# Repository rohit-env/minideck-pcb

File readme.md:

# Rohit's minideck PCB

so I went off and designed a whole cyberdeck pcb, it’s kinda sick, it's a full-on deck with ports, buttons, blinky stuff, and that clean hacker aesthetic. built it because laptops are boring and carrying around raw PCBs just hits different.the board’s got space for a pi, a couple usb ports, an oled, and some clicky switches. stuff’s laid out in a way that makes sense, but also makes you look like you’re about to jack into the matrix at a coffee shop. the idea is simple cram as much functional coolness as possible onto one board and still make it portable enough to flex at meetups. this whole thing started with a sketch on a sticky note and now it’s a real life project(obviously i need money to make it real). i even left space for expansion headers because future proofing or whatever. no idea how many late nights went into routing this lol

---

# features 

Uses Raspberry-pi CM4 form-factor for main SBC.

5inch or 4.3inch LCD display with support for another External Display out port.

Uses ESP32-S2 for all the secondary functions including keyboard and mouse control.

61 key customizable keyboard, 6 shoulder button for navigation.

3D hall-effect joystick is used for proper Mouse control.

10000mAh(21700) 2S battery can be used for main power source.

USB-PD 2Amps fast charging using USB-C port.

One USB-A and display out for external display.

USB-C formfactor Nurolink/docking port with UART, I2C.

---

| Image | Description |
|-------|-------------|
|  | top |

| Image | Description |
|-------|-------------|
|  | side |

| Image | Description |
|-------|-------------|
|  | top side |

| Image | Description |
|-------|-------------|
|  | main pcb render |

| Image | Description |
|-------|-------------|
|  | display pcb render |

| Image | Description |
|-------|-------------|
|  | main pcb |

| Image | Description |
|-------|-------------|
|   | display pcb |

----

# BOM

| **Component**            | **Description**                                                 | **Qty**     | **Estimated Price (USD)** | **Link** |
|--------------------------|-----------------------------------------------------------------|-------------|----------------------------|----------|
| **PCB**                  | Custom PCB                                           | 1           | $92 (without pcba after $20 coupon) | JLCPCB  |
| **4.3 inch display**     | Display for the deck                                            | 1           | $36.16                     | [Robocraze](https://robocraze.com/products/waveshare-4-3inch-dsi-lcd-capacitive-touch-display-800-480-for-raspberry-pi) |
| **21700 batteries**      | Batteries                                                       | 1 (pair)    | $10.41                     | [Drkstore](https://www.drkstore.in/molicel-inr-21700-p45b-3-6v-4500mah-10c-li-ion-battery/) |
| **5V Voltage Regulator** | Power regulator for the display                                 | 2           | $11.76                     | [Robocraze](https://robocraze.com/products/dfrobot-multi-output-dc-dc-buck-converter-module-3-3v-5v-9v-12v?variant=47357264396512) |
| **ESP32 Microcontroller**| Controls everything in the device (keyboard, mouse, etc.)       | 1           | $0                         | Already available |
| **Raspberry Pi Compute Module** | Heart of the device                                      | 1           | $80                        | [Robu](https://robu.in/product/raspberry-pi-compute-module-5-2gb-32gb/?gad_source=1&gad_campaignid=19974686076&gbraid=0AAAAADvLFWcZy6YV9cw0LotGvW8Dvi9Ij&gclid=CjwKCAjwkbzEBhAVEiwA4V-yqq5n8SdlHlythZ7EGNnsObi1siXfHtQSt-FhHNs-aKGvbE-3w4f5ixoC-zMQAvD_BwE) |

BOM: $229

# gallery

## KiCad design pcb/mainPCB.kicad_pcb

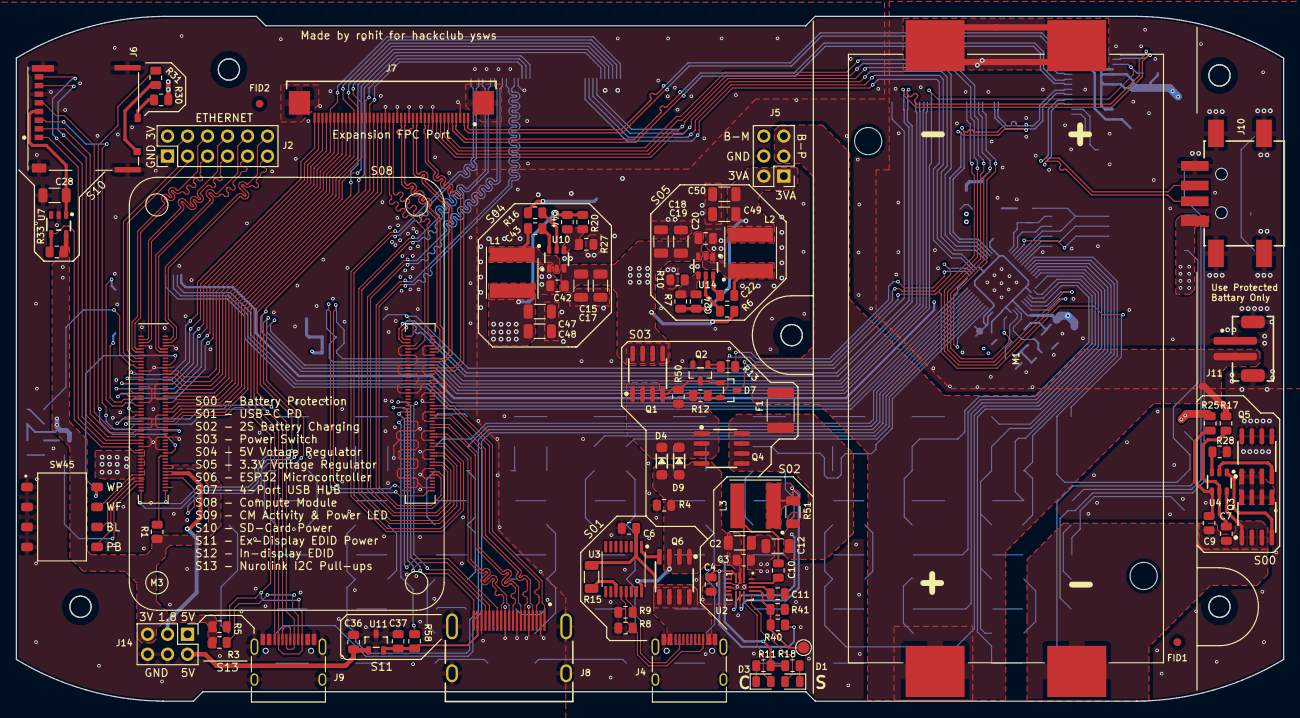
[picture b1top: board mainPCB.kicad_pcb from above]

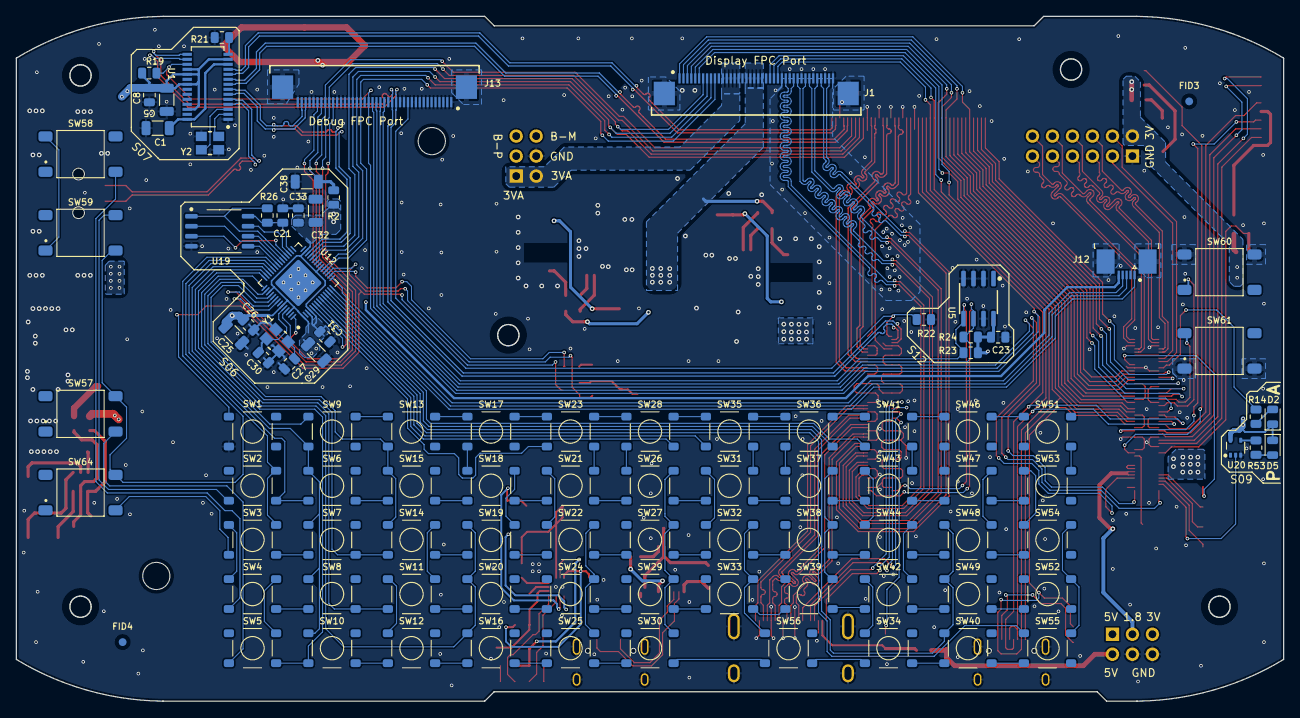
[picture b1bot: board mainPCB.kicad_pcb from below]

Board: 4 copper layers, 161.0 x 87.0 mm, 194 parts (97 on the bottom side), 260 nets.

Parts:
C1, C5, C15, C17, C18, C19, C25, C28, C29, C32, C38: 10uF; Capacitor-1206
C2, C12, C47, C48, C49, C50: 22uF; Capacitor-1206
C3, C4, C6, C11: 1uF; Capacitor-0805
C7, C8, C9, C10, C20, C21, C22, C23, C26, C31, C33, C36, C37, C42, C43: 0.1uF; Capacitor-0805
C24, C44: 100pF; Capacitor-0805
C27, C30: 16pF; Capacitor-0805
D1, D2, D3, D5: LED; LED-0805
D4, D9: MBR0540T3G; Diode-SOD-123
D7: BAT54C-(SOT23); SOT-23-3
F1: 0ZCG0260BF2B; Fuse-1812
FID1, FID2, FID3, FID4: Fiducial; Fiducial_1mm_Mask2mm
H1, H2, H3, H4, H5: MountingHole_Pad; MountingHole-M2.5-D2.7mm
J1, J7, J13: CF20401D0R0-NH; FPC-40-0.5mm-horizontal
J2: Conn_02x06-(RS2-12-G); PinHeader_2x06_P2.54mm_Vertical
J4, J9: 12402012E212A; USB_C-Female-(16-Pin)
J5, J14: Conn_02x03-(RS2-06-G); PinHeader_2x03_P2.54mm_Vertical
J6: Micro_SD_Card_Det; SD-Micro-Push-Push(MOLEX_503398-1892)
J8: HDMI_A-(2086581051); HDMI(EDAC 690-019-298-412)
J10: 629104190121; USB_A-horizontal-SMD-3
J11: B2B-PH-SM4-TB; JST-PH2-Vertical
J12: SFV5R-2STBE1HLF; FPC-5-0.5mm-horizontal
L1, L2: 10uH-(74404064100); Inductor-6.0x6.0xH4.5
L3: 6.8uH-(74404064068); Inductor-6.0x6.0xH4.5
M1: keystone-PN1048; Battery_holder-18650x2(keystone-PN1048)
M3: DF40C-100DS-0.4V(51); Module-ComputeModule4-CM4
Q1, Q4: DMP3037LSS-13; SOP-8
Q2: BCW66HVL-(2N2222); SOT-23-3
Q3, Q5: MOSFET-N; SOP-8
Q6: AOSP36326C; SOP-8
R1, R22, R28: 2.2k; Resistor-0805
R2, R3, R4, R5, R10, R12, R27, R40, R41, R50, R58: 10k; Resistor-0805
R6, R16, R19, R23, R24, R26, R33: 100k; Resistor-0805
R7: 33.2K; Resistor-0805
R8, R9: 5.1k; Resistor-0805
R11, R14, R18, R53: 1k; Resistor-0805
R13, R30, R31: 220R; Resistor-0805
R15: 5.1k; Resistor-1206
R17, R25: 330R; Resistor-0805
R20: 56.2k; Resistor-0805
R21: 2.7k; Resistor-0805
R51: 50mR; Resistor-1206
SW1, SW2, SW3, SW4, SW5, SW6, SW7, SW8, SW9, SW10, SW11, SW12, SW13, SW14, SW15, SW16, SW17, SW18, SW19, SW20, SW21, SW22, SW23, SW24, SW25, SW26, SW27, SW28, SW29, SW30, SW31, SW32, SW33, SW34, SW35, SW36, SW37, SW38, SW39, SW40, SW41, SW42, SW43, SW44, SW46, SW47, SW48, SW49, SW51, SW52, SW53, SW54, SW55, SW56: PTS526 SK15 SMTR2 LFS-(C&K); Switch-4x4x1.5-(PTS526)
SW45: Switch-6.2X4-DIP(DS04-254-2-04BK)
SW57, SW58, SW59, SW60, SW61, SW64: TS04-66-85-BK-160-SMT; Switch-6x6xXX-Extend
TP16: THERM; TestPoint-Pad_D1.5mm
U1: FE1.1S-BSOP28BCN; SSOP-28 (3.9x9.9x0.635)
U2: MP2615CGQ-Z-(QFN-16); QFN-16 (3x3-MP2615)
U3: IP2721-(TSSOP-16); TSSOP-16
U4: MM3220/S8252-(SOT-23-6); SOT-23-6
U5: AT24CM01-SSHM-B; SOP-8
U7: RT9742GGJ5; SOT-23-5
U10, U14: AP62300TWU-7-(SOT-23-6); SOT-23-6
U11: RT9742SNGV; SOT-23-3
U12: ESP32-S2FH4; QFN-56 (7x7x0.4)
U19: W25Q128JVS; SOIC-8-208mil
U20: 74LVC1G07SE-7-(SOT-353); SOT-353
Y1: 40mhz-(RH100-40.000-16-F-1010-TR); Crystal-3225-SMD
Y2: 12MHz-(RH100-12.000-12-1010-X-TR-NS2); Crystal-3225-SMD

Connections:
1: SW2.4, SW3.4, U12.38 (GPIO34)
1D+: J10.3 (D+), U1.5 (DP4)
1D-: J10.2 (D-), U1.4 (DM4)
2: SW6.3, SW7.3, SW8.3, SW9.1, SW10.3, U12.40 (GPIO36)
2D+: J13.39, U1.7 (DP3), U12.26 (GPIO20/USB_P)
2D-: J13.38, U1.6 (DM3), U12.25 (GPIO19/USB_N)
3: SW13.1, SW14.3, SW15.3, U12.47 (GPIO42)
3D+: J7.4, U1.9 (DP2)
3D-: J7.5, U1.8 (DM2)
4: SW16.3, SW19.3, SW20.3, U12.43 (GPIO39)
4D+: J7.1, U1.11 (DP1)
4D-: J7.2, U1.10 (DM1)
5: SW23.1, U12.6 (GPIO1)
6: SW28.2, U12.7 (GPIO2)
7: SW35.1, U12.8 (GPIO3)
8: SW36.2, U12.11 (GPIO6)
9: SW41.1, U12.12 (GPIO7)
10: SW40.3, SW48.3, SW49.3, U12.10 (GPIO5)
11: SW55.3, U12.9 (GPIO4)
12: SW57.4, SW59.2, SW64.4, U12.37 (GPIO33)
+3.3V: D2.A, D5.A, J2.2, J14.5, M3.84 (+3.3v_(Output)), M3.86 (+3.3v_(Output)), R1.1, R3.1, R5.1, R30.1, R33.1, U7.5 (IN), U20.5 (VCC)
+3.3VA: C5.1, C8.1, C24.2, C25.2, C26.2, C29.2, C31.2, C32.2, C33.2, C49.2, C50.2, J1.12, J1.13, J1.14, J1.15, J1.16, J5.1, J5.2, J12.5, L2.2, R2.2, R7.1, R19.2, U1.13 (VD33), U1.18 (VBUSM), U1.19 (BUSJ), U1.21 (VD33_O), U1.26 (OVCJ), U12.1 (VDDA), U12.3 (VDD3P3), U12.4 (VDD3P3), U12.20 (VDD3P3_RTC), U12.27 (VDD3P3_RTC_IO), U12.45 (VDD3P3_CPU), U12.51 (VDDA), U12.54 (VDDA)
+5V: C23.2, C36.1, C44.2, C47.2, C48.2, J10.1 (VBUS), J14.1, J14.2, L1.2, M3.77 (+5v_(Input)), M3.79 (+5v_(Input)), M3.81 (+5v_(Input)), M3.83 (+5v_(Input)), M3.85 (+5v_(Input)), M3.87 (+5v_(Input)), R20.1, R23.2, R24.2, U5.8 (VCC), U11.1 (IN)
+12V: C2.2, C3.2, D4.A, D9.A, Q4.4, Q6.1, Q6.2, Q6.3, R4.1, R11.2, R18.2, U2.2 (VIN), U3.16 (VBUS)
+BATT: F1.2, J5.3, J5.5, J11.2, M1.1, R17.1
+VDC: C12.2, F1.1, Q4.5, Q4.6, Q4.7, Q4.8, R51.1, U2.9 (BATT)
-BATT: C7.1, C9.1, M1.3, Q3.1, Q3.2, Q3.3, U4.6 (GND)
/+1.8v: J14.3, M3.88 (+1.8v_(Output)), M3.90 (+1.8v_(Output))
/ACOK: D1.C, U2.12 (*ACOK)
/Activity_LED: M3.21 (PI_nLED_Activity), R14.2
/BT_nDis: M3.91 (BT_nDisable), SW45.3B
/Charger_SW_Out: L3.1, R51.2, U2.10 (CSP)
/EEPROM_nWP: M3.20 (EEPROM_nWP), SW45.1B
/ETH_0_N: J2.9, M3.10 (Ethernet_Pair0_N)
/ETH_0_P: J2.10, M3.12 (Ethernet_Pair0_P)
/ETH_1_N: J2.11, M3.6 (Ethernet_Pair1_N)
/ETH_1_P: J2.12, M3.4 (Ethernet_Pair1_P)
/ETH_2_N: J2.5, M3.9 (Ethernet_Pair2_N)
/ETH_2_P: J2.6, M3.11 (Ethernet_Pair2_P)
/ETH_3_N: J2.7, M3.5 (Ethernet_Pair3_N)
/ETH_3_P: J2.8, M3.3 (Ethernet_Pair3_P)
/ETH_LEDG: J2.4, M3.17 (Ethernet_nLED2(3.3v))
/ETH_LEDY: J2.3, M3.15 (Ethernet_nLED3(3.3v))
/GLOBAL_EN: J13.21, M3.99 (Global_EN)
/GPIO2: J1.26, J7.26, J9.A5 (CC1), J9.B5 (CC2), M3.58 (GPIO2), R5.2
/GPIO3: J1.25, J7.27, J9.A8 (SBU1), J9.B8 (SBU2), M3.56 (GPIO3), R3.2
/GPIO4: J1.24, M3.54 (GPIO4)
/GPIO6: J7.31, M3.30 (GPIO6)
/GPIO7: J7.37, M3.37 (GPIO7)
/GPIO8: J1.1, J7.36, M3.39 (GPIO8)
/GPIO9: J1.3, J7.29, M3.40 (GPIO9)
/GPIO10: J1.4, J7.28, M3.44 (GPIO10)
/GPIO11: J1.2, J7.30, M3.38 (GPIO11)
/GPIO12: J7.38, M3.31 (GPIO12)
/GPIO13: J7.32, M3.28 (GPIO13)
/GPIO14: J7.25, J9.A7 (D-), J9.B7 (D-), M3.55 (GPIO14)
/GPIO15: J7.24, J9.A6 (D+), J9.B6 (D+), M3.51 (GPIO15)
/GPIO17: J1.5, M3.50 (GPIO17)
/GPIO18: J7.35, M3.49 (GPIO18)
/GPIO19: J7.33, M3.26 (GPIO19)
/GPIO20: J7.39, M3.27 (GPIO20)
/GPIO21: J7.40, M3.25 (GPIO21)
/GPIO24: M3.45 (GPIO24), SW60.1
/GPIO25: M3.41 (GPIO25), SW61.3
/GPIO26: J7.34, M3.24 (GPIO26)
/GPIO27: J1.6, M3.48 (GPIO27)
/GPIO_VREF: M3.78 (GPIO_VREF(1.8v/3.3v_Input)), R1.2
/HDMI0_CK_N: J1.28, M3.190 (HDMI0_CLK_N)
/HDMI0_CK_P: J1.30, M3.188 (HDMI0_CLK_P)
/HDMI0_D0_N: J1.31, M3.184 (HDMI0_TX0_N)
/HDMI0_D0_P: J1.33, M3.182 (HDMI0_TX0_P)
/HDMI0_D1_N: J1.34, M3.178 (HDMI0_TX1_N)
/HDMI0_D1_P: J1.36, M3.176 (HDMI0_TX1_P)
/HDMI0_D2_N: J1.37, M3.172 (HDMI0_TX2_N)
/HDMI0_D2_P: J1.39, M3.170 (HDMI0_TX2_P)
/HDMI0_HOTPLUG: M3.153 (HDMI0_HOTPLUG), R58.2
/HDMI0_SCL: J13.19, M3.200 (HDMI0_SCL), R24.1, U5.6 (SCL)
/HDMI0_SDA: J13.18, M3.199 (HDMI0_SDA), R23.1, U5.5 (SDA)
/HDMI1_CEC: J8.13 (CEC), M3.149 (HDMI1_CEC)
/HDMI1_CK_N: J8.12 (CK-), M3.166 (HDMI1_CLK_N)
/HDMI1_CK_P: J8.10 (CK+), M3.164 (HDMI1_CLK_P)
/HDMI1_D0_N: J8.9 (D0-), M3.160 (HDMI1_TX0_N)
/HDMI1_D0_P: J8.7 (D0+), M3.158 (HDMI1_TX0_P)
/HDMI1_D1_N: J8.6 (D1-), M3.154 (HDMI1_TX1_N)
/HDMI1_D1_P: J8.4 (D1+), M3.152 (HDMI1_TX1_P)
/HDMI1_D2_N: J8.3 (D2-), M3.148 (HDMI1_TX2_N)
/HDMI1_D2_P: J8.1 (D2+), M3.146 (HDMI1_TX2_P)
/HDMI1_HOTPLUG: J8.19 (HPD/HEAC-), M3.143 (HDMI1_HOTPLUG)
/HDMI1_SCL: J8.15 (SCL), M3.147 (HDMI1_SCL)
/HDMI1_SDA: J8.16 (SDA), M3.145 (HDMI1_SDA)
/HDMI_5v: C37.1, J8.18 (+5V), R58.1, U11.2 (OUT)
/PCIE_CLK_N: J7.17, M3.112 (PCIe_CLK_N)
/PCIE_CLK_P: J7.18, M3.110 (PCIe_CLK_P)
/PCIE_CLK_nREQ: J7.20, M3.102 (PCIe_CLK_nREQ)
/PCIE_RX_N: J7.14, M3.118 (PCIe_RX_N)
/PCIE_RX_P: J7.15, M3.116 (PCIe_RX_P)
/PCIE_TX_N: J7.11, M3.124 (PCIe_TX_N)
/PCIE_TX_P: J7.12, M3.122 (PCIe_TX_P)
/PCIE_nRST: J7.21, M3.109 (PCIe_nRST)
/PWR_LED: M3.95 (nPI_LED_PWR), U20.2
/RUN_PG: J13.20, M3.92 (RUN_PG)
/Reserved: M3.76 (Reserved), R31.1
/SD_CLK: J6.5 (CLK), M3.57 (SD_CLK)
/SD_CMD: J6.3 (CMD), M3.62 (SD_CMD)
/SD_DAT0: J6.7 (DAT0), M3.63 (SD_DAT0)
/SD_DAT1: J6.8 (DAT1), M3.67 (SD_DAT1)
/SD_DAT2: J6.1 (DAT2), M3.69 (SD_DAT2)
/SD_DAT3: J6.2 (DAT3/CD), M3.61 (SD_DAT3)
/SD_PWR: C28.2, J6.4 (VDD), U7.1 (OUT)
/SD_PWR_ON: M3.75 (SD_PWR_ON), R33.2, U7.4 (EN)
/USB2_N: J13.16, M3.103 (USB2_N), U1.15 (DMU)
/USB2_P: J13.15, M3.105 (USB2_P), U1.16 (DPU)
/USBOTG_ID: J13.12, M3.101 (USB_OTG_ID), R22.2
/WL_nDis: M3.89 (WiFi_nDisable), SW45.2B
/fb_3.3: C24.1, R7.2, R10.1, U14.4 (FB)
/fb_5: C44.1, R20.2, R27.1, U10.4 (FB)
/nEXTRST: J7.23, J13.22, M3.100 (nEXTRST), R19.1, U1.17 (~XRSTJ)
/nRPIBOOT: M3.93 (nRPIBOOT), SW45.4B
/sw3.3v: C22.2, L2.1, U14.2 (SW)
/sw5v: C43.2, L1.1, U10.2 (SW)
A: SW9.3, U12.41 (GPIO37)
B: SW2.2, SW6.1, U12.39 (GPIO35)
BAT_mid: J5.6, M1.2, M1.4, R25.1
BOOT0: J13.35, U12.5 (GPIO0)
BRIGTNESS_LCD: J1.10, J13.24, U12.18 (GPIO13)
BUT: J12.3, U12.14 (GPIO9)
C: SW7.2, SW14.1, U12.46 (GPIO41)
CC1: J4.A5 (CC1), R9.1, U3.13 (CC1)
CC2: J4.B5 (CC2), R8.1, U3.12 (CC2)
D: SW8.2, SW11.1, U12.44 (GPIO40)
E: SW5.2, SW10.1, U12.42 (GPIO38)
GND: C1.2, C2.1, C3.1, C4.1, C5.2, C6.1, C8.2, C11.1, C12.1, C15.1, C17.1, C18.1, C19.1, C20.2, C21.2, C23.1, C25.1, C26.1, C27.1, C28.1, C29.1, C30.1, C31.1, C32.1, C33.1, C36.2, C37.2, C38.1, C42.2, C47.1, C48.1, C49.1, C50.1, J1.27, J1.29, J1.32, J1.35, J1.38, J1.40, J1.Z1, J1.Z2, J2.1, J4.GND, J4.S, J5.4, J6.6 (VSS), J6.11 (SHIELD), J7.3, J7.10, J7.13, J7.16, J7.19, J7.22, J7.Z1, J7.Z2, J8.2 (D2S), J8.5 (D1S), J8.8 (D0S), J8.11 (CKS), J8.17 (GND), J8.SH1 (SH), J8.SH2 (SH), J8.SH3 (SH), J8.SH4 (SH), J9.GND, J9.S, J10.4 (GND), J10.S (SHIELD), J11.1, J11.Z1, J11.Z2, J12.2, J12.Z1, J12.Z2, J13.1, J13.2, J13.3, J13.4, J13.5, J13.6, J13.7, J13.8, J13.9, J13.10, J13.11, J13.13, J13.14, J13.17, J13.23, J13.28, J13.29, J13.30, J13.36, J13.37, J13.40, J13.Z1, J13.Z2, J14.4, J14.6, M3.1 (GND), M3.2 (GND), M3.7 (GND), M3.8 (GND), M3.13 (GND), M3.14 (GND), M3.22 (GND), M3.23 (GND), M3.32 (GND), M3.33 (GND), M3.42 (GND), M3.43 (GND), M3.52 (GND), M3.53 (GND), M3.59 (GND), M3.60 (GND), M3.65 (GND), M3.66 (GND), M3.71 (GND), M3.74 (GND), M3.98 (GND), M3.107 (GND), M3.108 (GND), M3.113 (GND), M3.114 (GND), M3.119 (GND), M3.120 (GND), M3.125 (GND), M3.126 (GND), M3.131 (GND), M3.132 (GND), M3.137 (GND), M3.138 (GND), M3.144 (GND), M3.150 (GND), M3.155 (GND), M3.156 (GND), M3.161 (GND), M3.162 (GND), M3.167 (GND), M3.168 (GND), M3.173 (GND), M3.174 (GND), M3.179 (GND), M3.180 (GND), M3.185 (GND), M3.186 (GND), M3.191 (GND), M3.192 (GND), M3.197 (GND), M3.198 (GND), Q2.2 (E), Q5.5, Q5.6, Q5.7, Q5.8, R4.2, R8.2, R9.2, R10.2, R21.1, R22.1, R27.2, R28.2, R41.2, SW1.1, SW45.1A, SW45.2A, SW45.3A, SW45.4A, SW60.3, SW60.4, SW61.1, SW61.2, U1.1 (VSS), U2.4 (CELL), U2.5 (SEL), U2.6 (*EN), U2.8 (AGND), U2.16 (PGND), U3.5 (GND), U5.2 (A1), U5.3 (A2), U5.4 (GND), U5.7 (WP), U7.2 (GND), U10.1 (GND), U11.3 (GND), U12.57 (GND), U14.1 (GND), U19.4 (GND), U20.3 (GND), Y1.2, Y1.4, Y2.2, Y2.4
HA: J12.1, U12.13 (GPIO8)
LDR: J1.9, J13.25, U12.19 (GPIO14)
unnamed: D1.A, R18.1
unnamed: D2.C, R14.1
unnamed: D3.A, R11.1
unnamed: D5.C, R53.1
unnamed: D7.1 (A1), Q1.4, Q2.3 (C), R50.1
unnamed: J6.10 (DET_A), R30.2
unnamed: J6.9 (DET_B), R31.2
unnamed: Q2.1 (B), R13.1
unnamed: Q3.5, Q3.6, Q3.7, Q3.8, Q5.1, Q5.2, Q5.3
unnamed: R53.2, U20.4
unnamed: SW2.1, SW59.4
unnamed: SW3.1, SW64.2
unnamed: SW3.2, SW7.1
unnamed: SW3.3, SW4.3
unnamed: SW4.1, SW58.2
unnamed: SW4.2, SW8.1
unnamed: SW4.4, SW5.4
unnamed: SW5.1, SW57.2
unnamed: SW10.2, SW12.1
unnamed: SW11.2, SW20.1
unnamed: SW11.3, SW12.3
unnamed: SW11.4, SW14.4
unnamed: SW12.2, SW16.1
unnamed: SW9.4, SW13.3
unnamed: SW13.4, SW17.3
unnamed: SW14.2, SW19.1
unnamed: SW6.2, SW15.1
unnamed: SW15.2, SW18.1
unnamed: SW16.2, SW25.1
unnamed: SW17.1, SW18.3
unnamed: SW17.4, SW23.3
unnamed: SW18.2, SW21.1
unnamed: SW18.4, SW19.4
unnamed: SW19.2, SW22.1
unnamed: SW20.2, SW24.1
unnamed: SW21.2, SW26.1
unnamed: SW21.3, SW22.3
unnamed: SW21.4, SW23.2
unnamed: SW22.2, SW27.1
unnamed: SW22.4, SW24.4, SW25.4
unnamed: SW23.4, SW28.3
unnamed: SW24.2, SW29.1
unnamed: SW25.2, SW30.1
unnamed: SW26.2, SW31.1
unnamed: SW26.3, SW28.1
unnamed: SW26.4, SW27.4, SW29.4, SW30.4
unnamed: SW27.2, SW32.1
unnamed: SW28.4, SW35.3
unnamed: SW29.2, SW33.1
unnamed: SW30.2, SW56.1
unnamed: SW31.2, SW37.1
unnamed: SW31.3, SW32.3
unnamed: SW31.4, SW35.2
unnamed: SW32.2, SW38.1
unnamed: SW32.4, SW33.4, SW56.3
unnamed: SW33.2, SW39.1
unnamed: SW34.1, SW56.2
unnamed: SW34.2, SW40.1
unnamed: SW34.3, SW42.3
unnamed: SW35.4, SW36.3
unnamed: SW36.1, SW37.3
unnamed: SW36.4, SW41.3
unnamed: SW37.2, SW43.1
unnamed: SW37.4, SW38.4, SW39.4
unnamed: SW38.2, SW44.1
unnamed: SW39.2, SW42.1
unnamed: SW40.2, SW55.1
unnamed: SW41.2, SW43.4
unnamed: SW41.4, SW46.3
unnamed: SW42.2, SW49.1
unnamed: SW42.4, SW44.4
unnamed: SW43.2, SW47.1
unnamed: SW43.3, SW44.3
unnamed: SW44.2, SW48.1
unnamed: SW46.1, SW47.3
unnamed: SW46.4, SW51.3
unnamed: SW47.2, SW53.1
unnamed: SW47.4, SW48.4
unnamed: SW48.2, SW54.1
unnamed: SW49.2, SW52.1
unnamed: SW51.2, SW53.4
unnamed: SW52.4, SW54.4, SW55.4
unnamed: SW53.3, SW54.3
unnamed: SW58.3, SW59.1
unnamed: R21.2, U1.14 (REXT)
unnamed: C1.1, U1.12 (VD18_O), U1.28 (VD18)
unnamed: U1.3 (XIN), Y2.3
unnamed: U1.2 (XOUT), Y2.1
unnamed: D3.C, U2.11 (*CHGOK)
unnamed: C10.1, U2.15 (BST)
unnamed: C10.2, L3.2, U2.1 (SW)
unnamed: C11.2, U2.14 (TMR)
unnamed: C4.2, R40.1, U2.3 (VCC)
unnamed: R15.2, U3.11 (SEL)
unnamed: Q5.4, U4.2 (COUT)
unnamed: Q3.4, U4.1 (DOUT)
unnamed: R28.1, U4.3 (V-)
unnamed: C9.2, R25.2, U4.4 (VBL)
unnamed: C7.2, R17.2, U4.5 (VDD)
unnamed: C43.1, U10.6 (BOOT)
unnamed: R16.2, U10.5 (EN)
unnamed: C22.1, U14.6 (BOOT)
unnamed: R6.2, U14.5 (EN)
POWER: D4.C, D9.C, Q1.1, Q1.2, Q1.3, Q4.1, Q4.2, Q4.3, R12.1, R50.2
POWER_BUTTON: D7.3 (CC), J13.31, SW1.3
POWER_BUTTON_DETECT: D7.2 (A2), R12.2, U12.17 (GPIO12)
POWER_MAIN: R13.2, U12.16 (GPIO11)
Power_Out: C15.2, C17.2, C18.2, C19.2, C20.1, C42.1, J1.18, J1.19, J1.20, J1.21, J1.22, Q1.5, Q1.6, Q1.7, Q1.8, R6.1, R16.1, U10.3 (VIN), U14.3 (VIN)
RX-ESP: J7.7, J13.32, U12.49 (U0RXD)
SCL-ESP: J1.8, J7.9, J13.26, U12.23 (GPIO17/DAC_1)
SDA-ESP: J1.7, J7.8, J13.27, U12.24 (GPIO18/DAC_2)
SPICLK: U12.34 (SPICLK), U19.6 (CLK)
SPICS0: R26.2, U12.33 (SPICS0), U19.1 (~CS)
SPID: U12.36 (SPID), U19.5 (DI(IO0))
SPIHD: U12.31 (SPIHD), U19.7 (IO3)
SPIQ: U12.35 (SPIQ), U19.2 (DO(IO1))
SPIWP: U12.32 (SPIWP), U19.3 (IO2)
TX-ESP: J7.6, J13.33, U12.48 (U0TXD)
Thermistor 2: R40.2, R41.1, TP16.1, U2.13 (NTC)
VA: J12.4, U12.15 (GPIO10)
VBUS: C6.2, J4.VBUS, Q6.5, Q6.6, Q6.7, Q6.8, R15.1, U3.2 (VIN)
VBUS_EN: Q6.4, U3.1 (VBUSG)
VDD_SPI: C21.1, R26.1, U12.30 (VDD_SPI), U19.8 (VCC)
XTAL_N: C30.2, U12.52 (XTAL_N), Y1.3
XTAL_P: C27.2, U12.53 (KTAL_P), Y1.1
~RESET: C38.2, J13.34, R2.1, U12.56 (CHIP_PU)

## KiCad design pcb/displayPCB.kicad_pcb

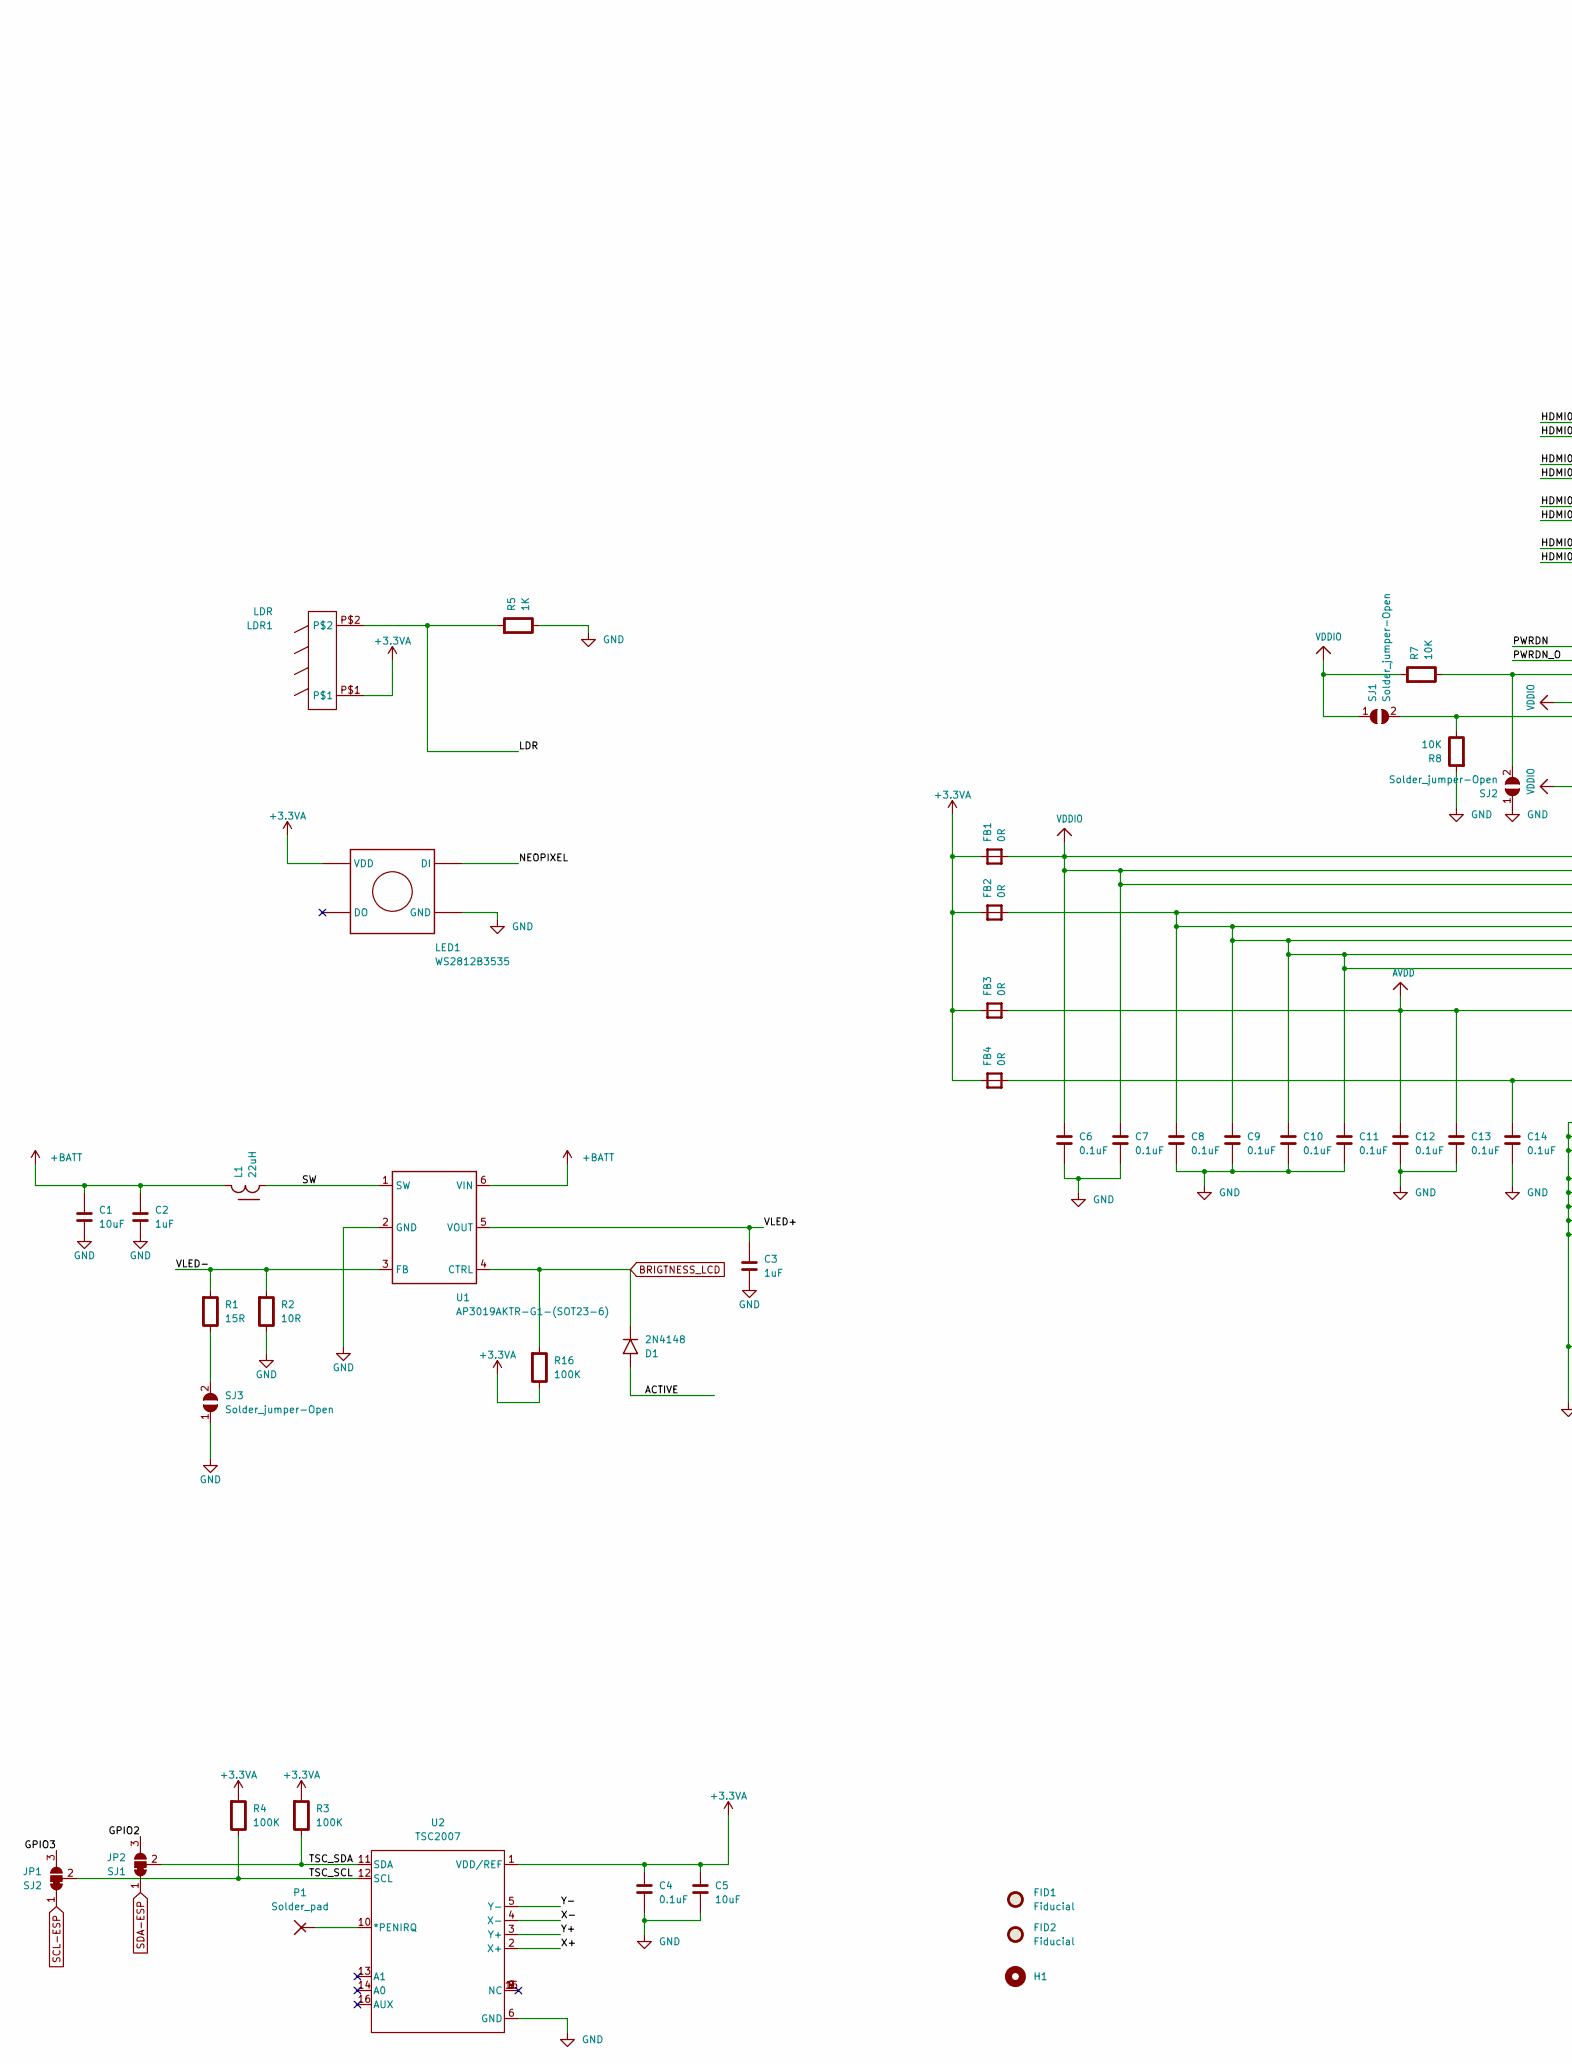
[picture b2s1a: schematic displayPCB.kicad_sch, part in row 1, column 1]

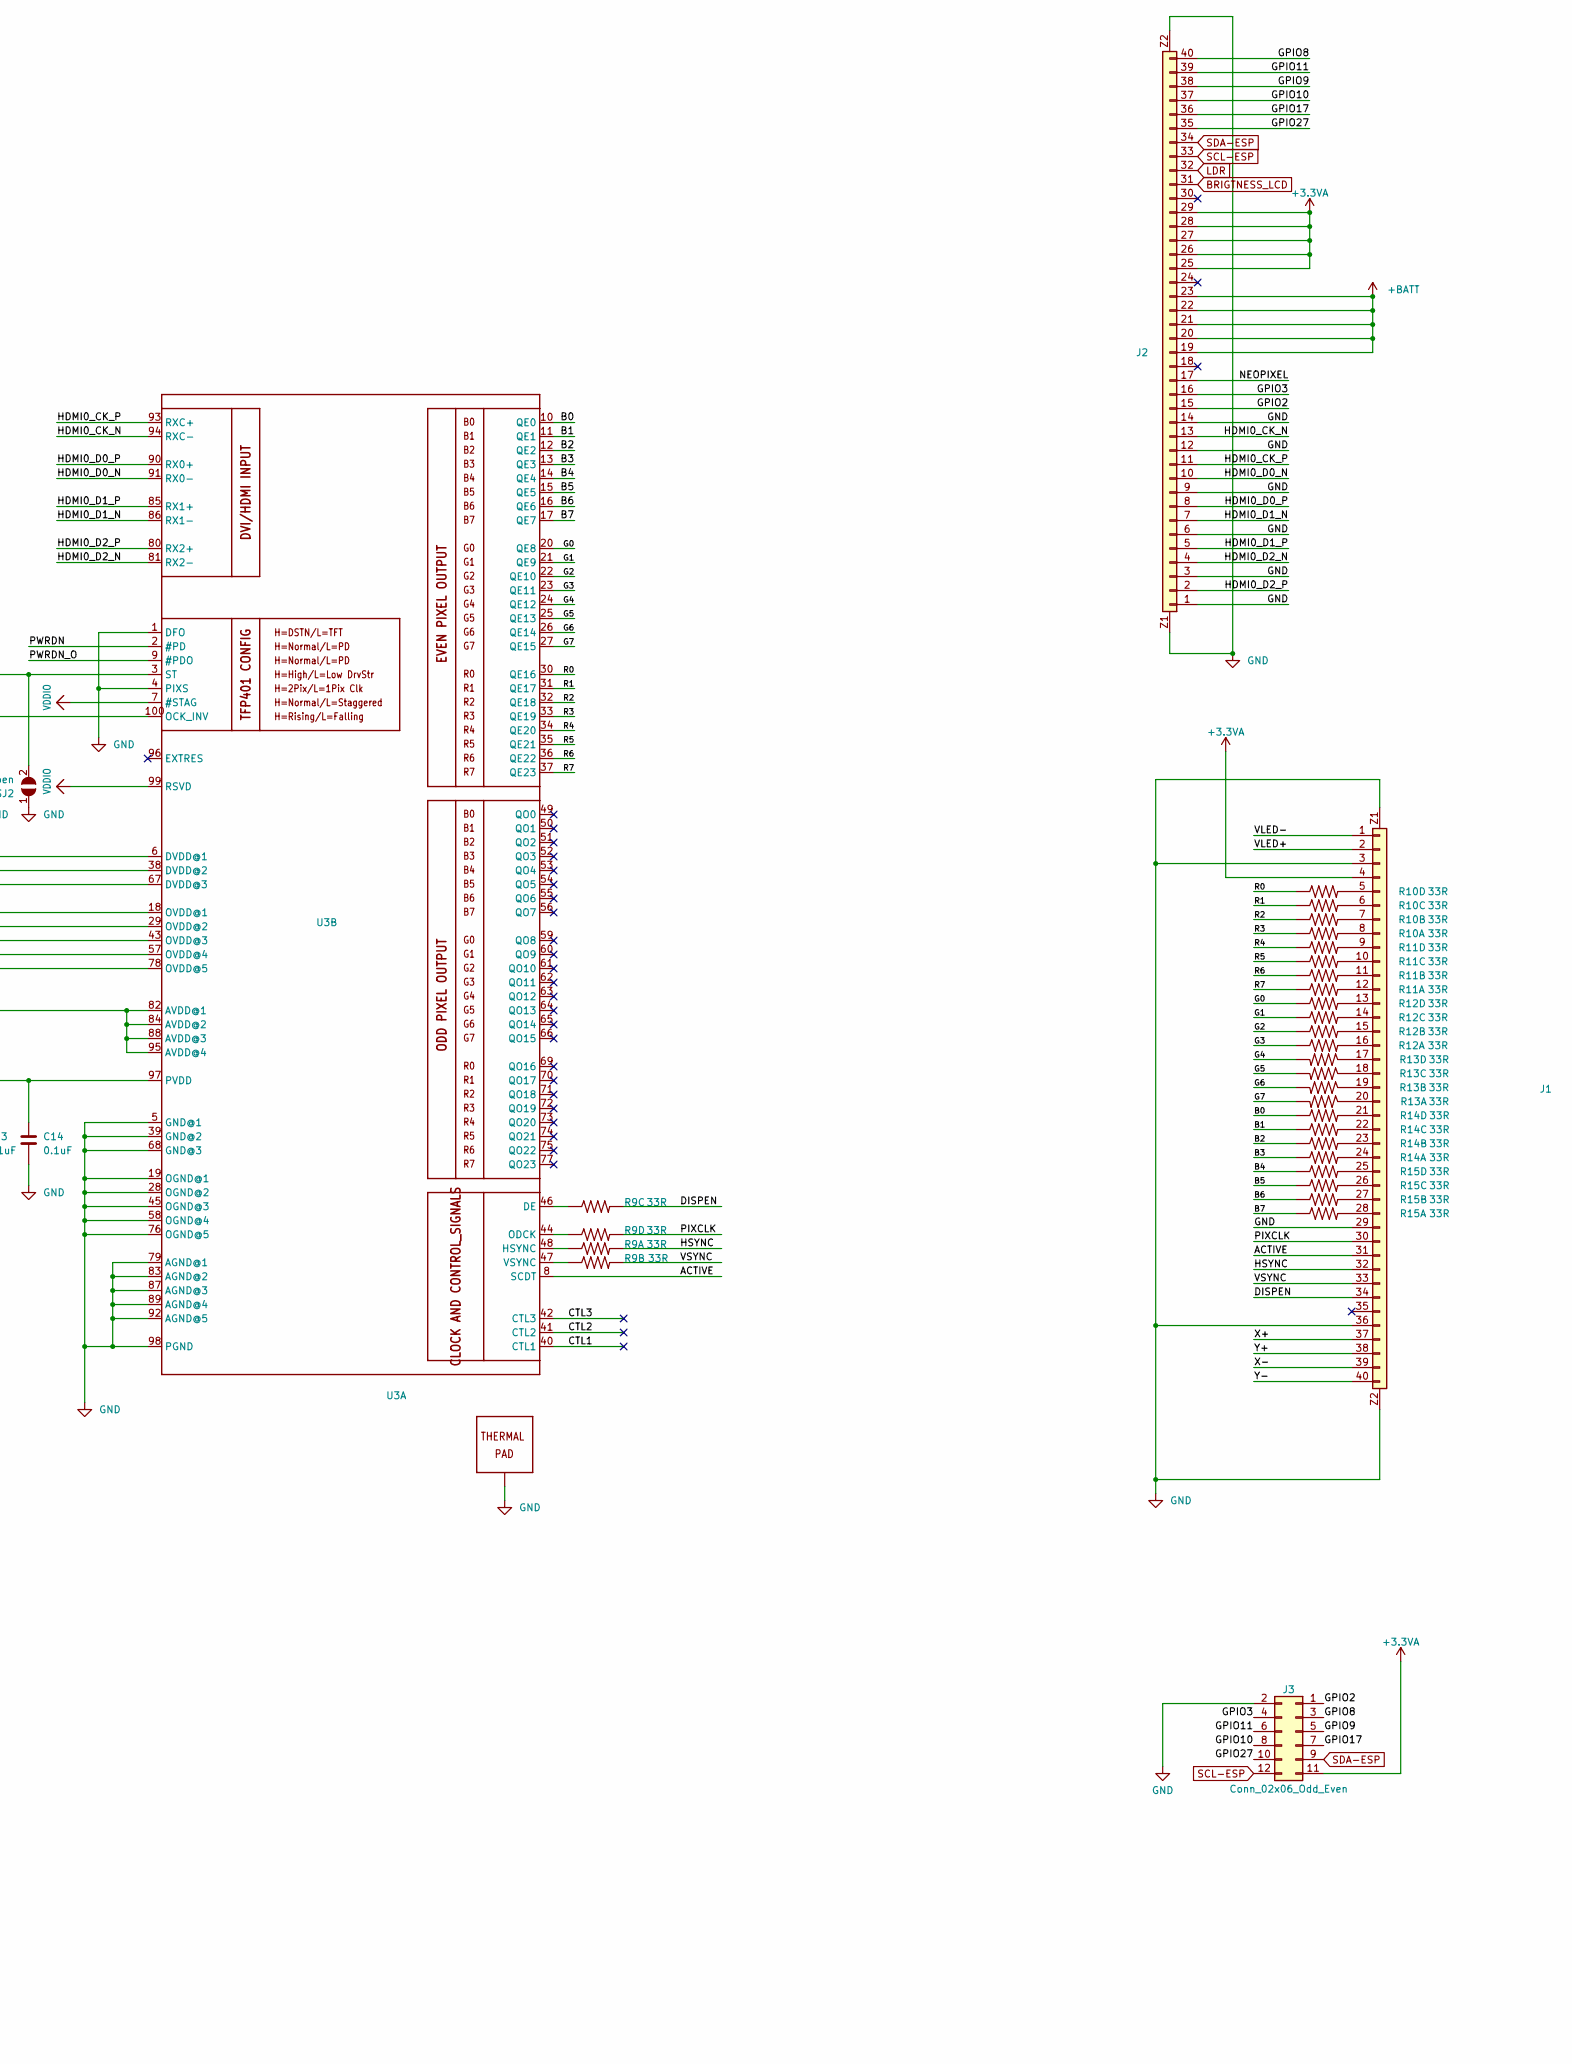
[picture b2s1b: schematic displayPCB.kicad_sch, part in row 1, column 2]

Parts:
C1, C5: 10uF; Capacitor-1206
C2, C3: 1uF; Capacitor-0805
C4, C6, C7, C8, C9, C10, C11, C12, C13, C14: 0.1uF; Capacitor-0805
D1: 2N4148; Diode-SOD-323
FB1, FB2, FB3, FB4: 0R; Ferrite-0805
FID1, FID2: Fiducial; Fiducial_1mm_Mask2mm
H1: MountingHole_Pad; MountingHole_5.3mm_M5
J1, J2: FPC-40; FPC-40-0.5mm-horizontal
J3: Conn_02x06_Odd_Even; PinHeader_2x06_P2.54mm_Vertical
JP1: SJ2; SolderJumper-3_P1.3mm_Bridged12_RoundedPad1.0x1.5mm
JP2: SJ1; SolderJumper-3_P1.3mm_Bridged12_RoundedPad1.0x1.5mm
L1: 22uH; Inductor-4.0x4.0_H3
LDR1: LDR; LDR-5506-D5mm
LED1: WS2812B3535; LED-3535(WS2812B)
P1: Solder_pad; TestPoint-Pad_D1.5mm
R1: 15R; Resistor-0805
R2: 10R; Resistor-0805
R3, R4, R16: 100K; Resistor-0805
R5: 1K; Resistor-0805
R7, R8: 10K; Resistor-0805
R9, R10, R11, R12, R13, R14, R15: 33R; Resistor-4x0603
SJ1, SJ2, SJ3: Solder_jumper-Open; SolderJumper-Open
U1: AP3019AKTR-G1-(SOT23-6); SOT-23-6
U2: TSC2007; TSSOP-16
U3: TFP401-(QFP-100); QFP-100

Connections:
+3.3VA: C4.1, C5.1, FB1.2, FB2.2, FB3.2, FB4.2, J1.4, J2.25, J2.26, J2.27, J2.28, J2.29, J3.11, LDR1.P$1, LED1.3 (VDD), R3.1, R4.1, R16.2, U2.1 (VDD/REF)
+BATT: C1.2, C2.2, J2.19, J2.20, J2.21, J2.22, J2.23, L1.1, U1.6 (VIN)
/ACTIVE: D1.A, J1.31, U3.8 (SCDT)
/B0: R14.4 (1), U3.10 (QE0)
/B1: R14.3 (1), U3.11 (QE1)
/B2: R14.2 (1), U3.12 (QE2)
/B3: R14.1, U3.13 (QE3)
/B4: R15.4 (1), U3.14 (QE4)
/B5: R15.3 (1), U3.15 (QE5)
/B6: R15.2 (1), U3.16 (QE6)
/B7: R15.1, U3.17 (QE7)
/CTL1: U3.40 (CTL1)
/CTL2: U3.41 (CTL2)
/CTL3: U3.42 (CTL3)
/DISPEN: J1.34, R9.6 (2)
/G0: R12.4 (1), U3.20 (QE8)
/G1: R12.3 (1), U3.21 (QE9)
/G2: R12.2 (1), U3.22 (QE10)
/G3: R12.1, U3.23 (QE11)
/G4: R13.5 (2), U3.24 (QE12)
/G5: R13.6 (2), U3.25 (QE13)
/G6: R13.7 (2), U3.26 (QE14)
/G7: R13.8 (2), U3.27 (QE15)
/GPIO2: J2.15, J3.1, JP2.3 (B)
/GPIO3: J2.16, J3.4, JP1.3 (B)
/GPIO8: J2.40, J3.3
/GPIO9: J2.38, J3.5
/GPIO10: J2.37, J3.8
/GPIO11: J2.39, J3.6
/GPIO17: J2.36, J3.7
/GPIO27: J2.35, J3.10
/HDMI0_CK_N: J2.13, U3.94 (RXC-)
/HDMI0_CK_P: J2.11, U3.93 (RXC+)
/HDMI0_D0_N: J2.10, U3.91 (RX0-)
/HDMI0_D0_P: J2.8, U3.90 (RX0+)
/HDMI0_D1_N: J2.7, U3.86 (RX1-)
/HDMI0_D1_P: J2.5, U3.85 (RX1+)
/HDMI0_D2_N: J2.4, U3.81 (RX2-)
/HDMI0_D2_P: J2.2, U3.80 (RX2+)
/HSYNC: J1.32, R9.8 (2)
/NEOPIXEL: J2.17, LED1.2 (DI)
/PIXCLK: J1.30, R9.5 (2)
/PWRDN: U3.2 (#PD)
/PWRDN_O: U3.9 (#PDO)
/R0: R10.4 (1), U3.30 (QE16)
/R1: R10.3 (1), U3.31 (QE17)
/R2: R10.2 (1), U3.32 (QE18)
/R3: R10.1, U3.33 (QE19)
/R4: R11.4 (1), U3.34 (QE20)
/R5: R11.3 (1), U3.35 (QE21)
/R6: R11.2 (1), U3.36 (QE22)
/R7: R11.1, U3.37 (QE23)
/SW: L1.2, U1.1 (SW)
/TSC_SCL: JP1.2 (C), R4.2, U2.12 (SCL)
/TSC_SDA: JP2.2 (C), R3.2, U2.11 (SDA)
/VLED+: C3.2, J1.2, U1.5 (VOUT)
/VLED-: J1.1, R1.1, R2.1, U1.3 (FB)
/VSYNC: J1.33, R9.7 (2)
/X+: J1.37, U2.2 (X+)
/X-: J1.39, U2.4 (X-)
/Y+: J1.38, U2.3 (Y+)
/Y-: J1.40, U2.5 (Y-)
AVDD: C12.1, C13.1, FB3.1, U3.82 (AVDD@1), U3.84 (AVDD@2), U3.88 (AVDD@3), U3.95 (AVDD@4)
BRIGTNESS_LCD: D1.C, J2.31, R16.1, U1.4 (CTRL)
GND: C1.1, C2.1, C3.1, C4.2, C5.2, C6.2, C7.2, C8.2, C9.2, C10.2, C11.2, C12.2, C13.2, C14.2, J1.3, J1.29, J1.36, J1.Z1, J1.Z2, J2.1, J2.3, J2.6, J2.9, J2.12, J2.14, J2.Z1, J2.Z2, J3.2, LED1.1 (GND), R2.2, R5.2, R8.1, SJ2.1, SJ3.1, U1.2 (GND), U2.6 (GND), U3.1 (DFO), U3.4 (PIXS), U3.5 (GND@1), U3.19 (OGND@1), U3.28 (OGND@2), U3.39 (GND@2), U3.45 (OGND@3), U3.58 (OGND@4), U3.68 (GND@3), U3.76 (OGND@5), U3.79 (AGND@1), U3.83 (AGND@2), U3.87 (AGND@3), U3.89 (AGND@4), U3.92 (AGND@5), U3.98 (PGND), U3.P$1 (TP), U3.P$2 (TP), U3.P$3 (TP), U3.P$4 (TP), U3.P$5 (TP), U3.P$6 (TP), U3.P$7 (TP), U3.P$8 (TP), U3.P$9 (TP), U3.P$10 (TP), U3.P$11 (TP), U3.P$12 (TP), U3.P$13 (TP), U3.P$14 (TP), U3.P$15 (TP), U3.P$16 (TP), U3.T (TP)
LDR: J2.32, LDR1.P$2, R5.1
unnamed: J1.5, R10.5 (2)
unnamed: J1.6, R10.6 (2)
unnamed: J1.7, R10.7 (2)
unnamed: J1.8, R10.8 (2)
unnamed: J1.9, R11.5 (2)
unnamed: J1.10, R11.6 (2)
unnamed: J1.11, R11.7 (2)
unnamed: J1.12, R11.8 (2)
unnamed: J1.13, R12.5 (2)
unnamed: J1.14, R12.6 (2)
unnamed: J1.15, R12.7 (2)
unnamed: J1.16, R12.8 (2)
unnamed: J1.17, R13.4 (1)
unnamed: J1.18, R13.3 (1)
unnamed: J1.19, R13.2 (1)
unnamed: J1.20, R13.1
unnamed: J1.21, R14.5 (2)
unnamed: J1.22, R14.6 (2)
unnamed: J1.23, R14.7 (2)
unnamed: J1.24, R14.8 (2)
unnamed: J1.25, R15.5 (2)
unnamed: J1.26, R15.6 (2)
unnamed: J1.27, R15.7 (2)
unnamed: J1.28, R15.8 (2)
unnamed: P1.1, U2.10 (*PENIRQ)
unnamed: R1.2, SJ3.2
unnamed: R9.2 (1), U3.47 (VSYNC)
unnamed: R9.3 (1), U3.46 (DE)
unnamed: R9.4 (1), U3.44 (ODCK)
unnamed: R9.1, U3.48 (HSYNC)
unnamed: R8.2, SJ1.2, U3.100 (OCK_INV)
unnamed: C8.1, C9.1, C10.1, C11.1, FB2.1, U3.18 (OVDD@1), U3.29 (OVDD@2), U3.43 (OVDD@3), U3.57 (OVDD@4), U3.78 (OVDD@5)
unnamed: C14.1, FB4.1, U3.97 (PVDD)
unnamed: R7.2, SJ2.2, U3.3 (ST)
SCL-ESP: J2.33, J3.12, JP1.1 (A)
SDA-ESP: J2.34, J3.9, JP2.1 (A)
VDDIO: C6.1, C7.1, FB1.1, R7.1, SJ1.1, U3.6 (DVDD@1), U3.7 (#STAG), U3.38 (DVDD@2), U3.67 (DVDD@3), U3.99 (RSVD)
